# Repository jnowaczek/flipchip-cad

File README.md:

# flipchip-cad

## MM24I Extended Memory
NVSRAM-based replacement for 24 kiloword PDP-12 core memory expansion normally accomplished with an expansion chassis and up to 6 MM8I modules. This design is potentially compatible with PDP-8i machines, although the memory timing signals are slightly different. Requires appropriate Memory Extension Control module (MC12 for the PDP-12).

## Signal Cable Connector W021J
Flat-flex cable version of the W021 intended for use with the MM24I

## Flip Chip Slot Breakout P111
First attempt at PCB design, intended to simplify probing a PDP backplane with an oscilloscope

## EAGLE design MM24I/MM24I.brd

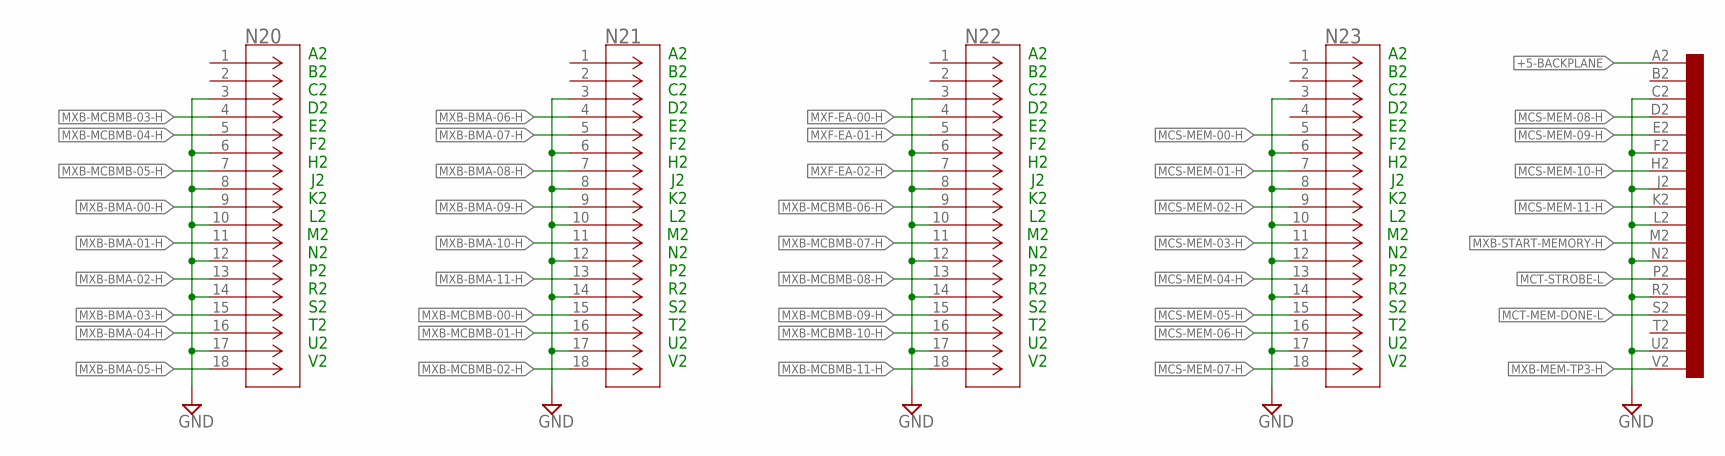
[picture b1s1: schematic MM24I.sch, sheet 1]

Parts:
N20, N21, N22, N23: FH12-18S-0.5SV(55); CON18_1X18_DUTB_HRS
U$1: SINGLE; EDGE-CON2

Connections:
+5-BACKPLANE: U$1.A2; also elsewhere on the board
GND: N20.3, N20.6, N20.8, N20.10, N20.12, N20.14, N20.17, N21.3, N21.6, N21.8, N21.10, N21.12, N21.14, N21.17, N22.3, N22.6, N22.8, N22.10, N22.12, N22.14, N22.17, N23.3, N23.6, N23.8, N23.10, N23.12, N23.14, N23.17, U$1.C2, U$1.F2, U$1.J2, U$1.L2, U$1.N2, U$1.R2, U$1.U2; also elsewhere on the board
MCS-MEM-00-H: N23.5; also elsewhere on the board
MCS-MEM-01-H: N23.7; also elsewhere on the board
MCS-MEM-02-H: N23.9; also elsewhere on the board
MCS-MEM-03-H: N23.11; also elsewhere on the board
MCS-MEM-04-H: N23.13; also elsewhere on the board
MCS-MEM-05-H: N23.15; also elsewhere on the board
MCS-MEM-06-H: N23.16; also elsewhere on the board
MCS-MEM-07-H: N23.18; also elsewhere on the board
MCS-MEM-08-H: U$1.D2; also elsewhere on the board
MCS-MEM-09-H: U$1.E2; also elsewhere on the board
MCS-MEM-10-H: U$1.H2; also elsewhere on the board
MCS-MEM-11-H: U$1.K2; also elsewhere on the board
MCT-MEM-DONE-L: U$1.S2; also elsewhere on the board
MCT-STROBE-L: U$1.P2; also elsewhere on the board
MXB-BMA-00-H: N20.9; also elsewhere on the board
MXB-BMA-01-H: N20.11; also elsewhere on the board
MXB-BMA-02-H: N20.13; also elsewhere on the board
MXB-BMA-03-H: N20.15; also elsewhere on the board
MXB-BMA-04-H: N20.16; also elsewhere on the board
MXB-BMA-05-H: N20.18; also elsewhere on the board
MXB-BMA-06-H: N21.4; also elsewhere on the board
MXB-BMA-07-H: N21.5; also elsewhere on the board
MXB-BMA-08-H: N21.7; also elsewhere on the board
MXB-BMA-09-H: N21.9; also elsewhere on the board
MXB-BMA-10-H: N21.11; also elsewhere on the board
MXB-BMA-11-H: N21.13; also elsewhere on the board
MXB-MCBMB-00-H: N21.15; also elsewhere on the board
MXB-MCBMB-01-H: N21.16; also elsewhere on the board
MXB-MCBMB-02-H: N21.18; also elsewhere on the board
MXB-MCBMB-03-H: N20.4; also elsewhere on the board
MXB-MCBMB-04-H: N20.5; also elsewhere on the board
MXB-MCBMB-05-H: N20.7; also elsewhere on the board
MXB-MCBMB-06-H: N22.9; also elsewhere on the board
MXB-MCBMB-07-H: N22.11; also elsewhere on the board
MXB-MCBMB-08-H: N22.13; also elsewhere on the board
MXB-MCBMB-09-H: N22.15; also elsewhere on the board
MXB-MCBMB-10-H: N22.16; also elsewhere on the board
MXB-MCBMB-11-H: N22.18; also elsewhere on the board
MXB-MEM-TP3-H: U$1.V2; also elsewhere on the board
MXB-START-MEMORY-H: U$1.M2; also elsewhere on the board
MXF-EA-00-H: N22.4; also elsewhere on the board
MXF-EA-01-H: N22.5; also elsewhere on the board
MXF-EA-02-H: N22.7; also elsewhere on the board

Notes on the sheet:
A2 B2 C2 D2 E2 F2 H2 J2 K2 L2 M2 N2 P2 R2 S2 T2 U2 V2

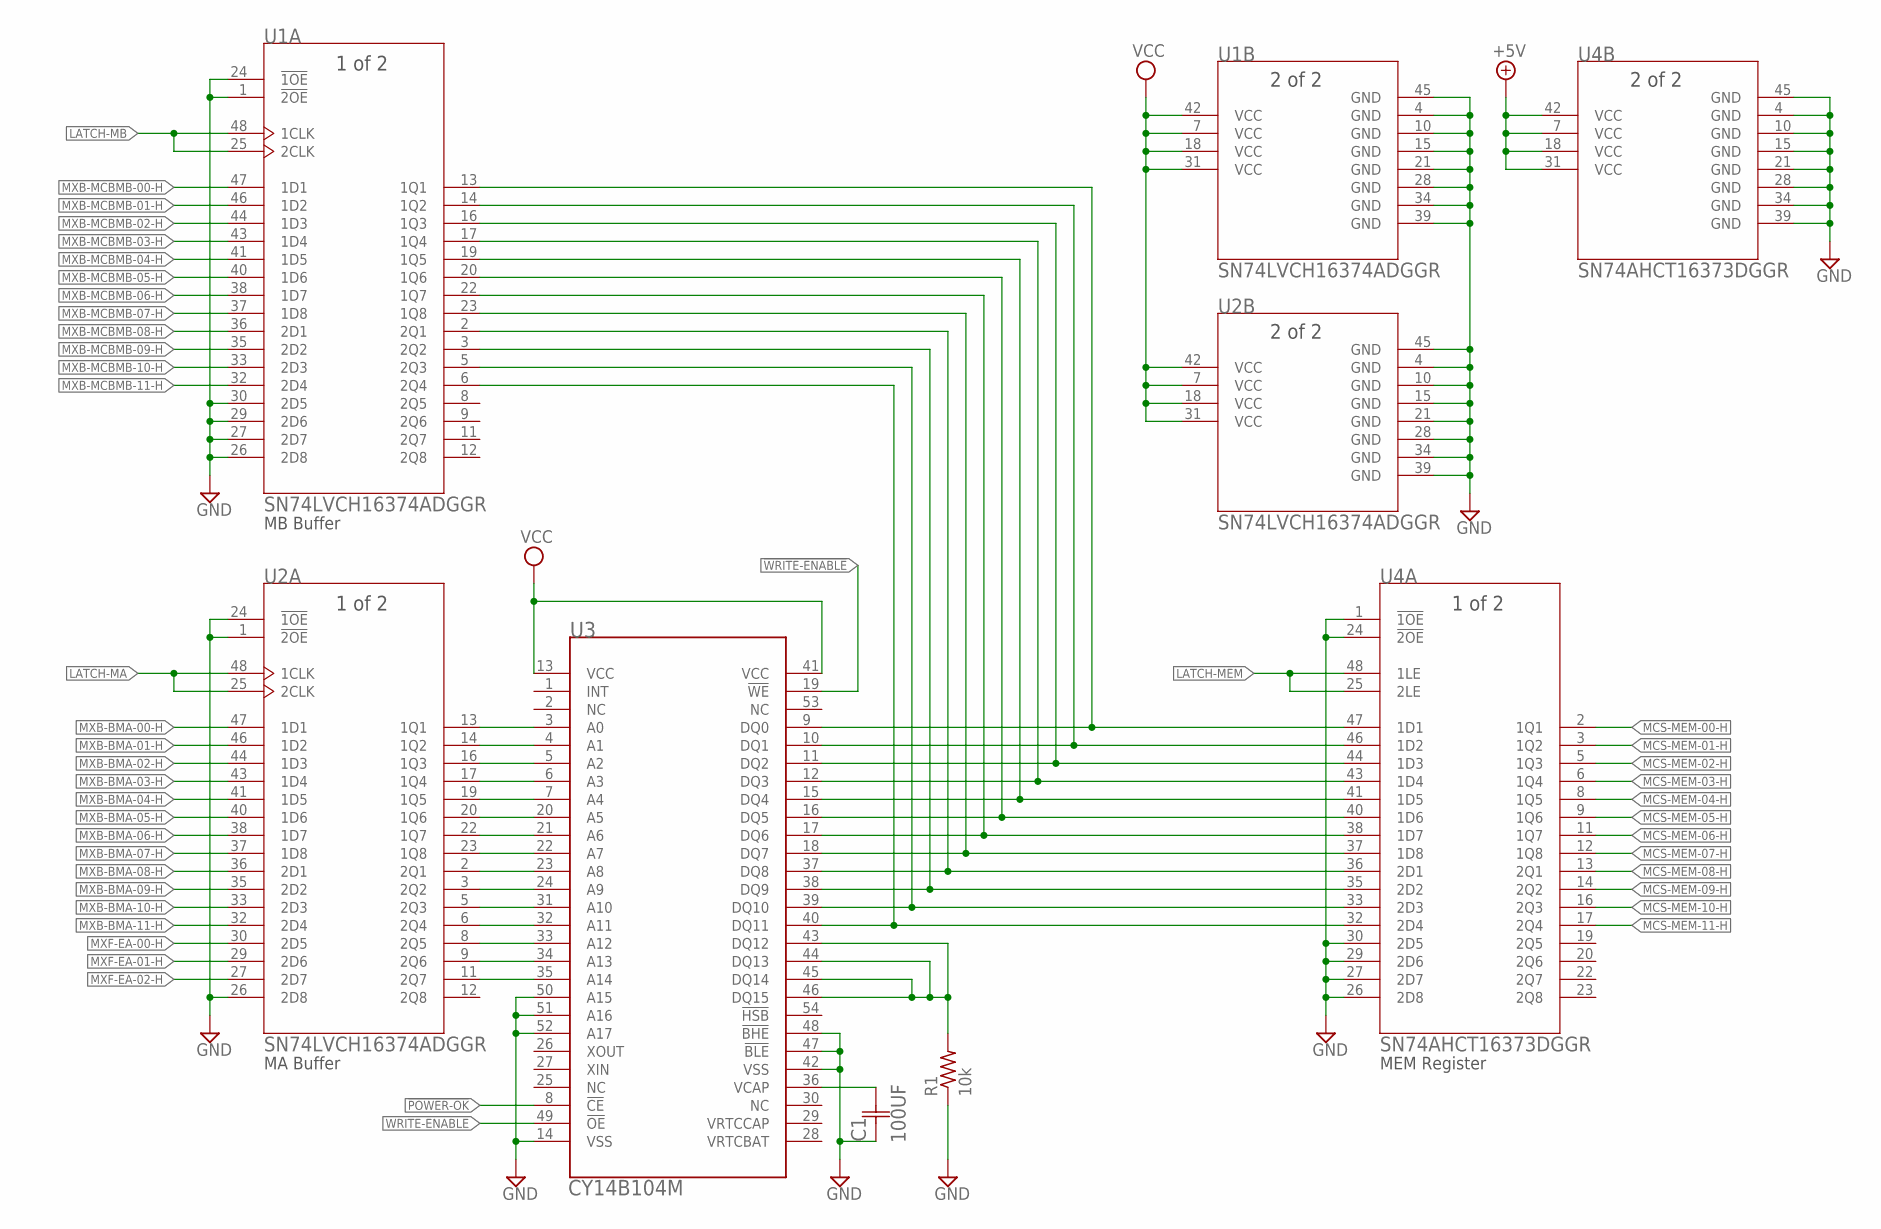
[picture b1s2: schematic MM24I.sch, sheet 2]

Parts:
C1: 100UF; CAPCP7343X430N
R1: 10k; R0402
U1, U2: SN74LVCH16374ADGGR; DGG48
U3: CY14B104M; TSOPII-54
U4: SN74AHCT16373DGGR; DGG48

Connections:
!POWER-OK: U3.8 (!CE); also elsewhere on the board
!WRITE-ENABLE: U3.19 (!WE); also elsewhere on the board
+5V: U4.7 (VCC), U4.18 (VCC), U4.31 (VCC), U4.42 (VCC); also elsewhere on the board
GND: C1.2 (C2), R1.1, U1.1 (!2OE), U1.4 (GND), U1.10 (GND), U1.15 (GND), U1.21 (GND), U1.24 (!1OE), U1.26 (2D8), U1.27 (2D7), U1.28 (GND), U1.29 (2D6), U1.30 (2D5), U1.34 (GND), U1.39 (GND), U1.45 (GND), U2.1 (!2OE), U2.4 (GND), U2.10 (GND), U2.15 (GND), U2.21 (GND), U2.24 (!1OE), U2.26 (2D8), U2.28 (GND), U2.34 (GND), U2.39 (GND), U2.45 (GND), U3.14 (VSS), U3.42 (VSS), U3.47 (!BLE), U3.48 (!BHE), U3.50 (A15), U3.51 (A16), U3.52 (A17), U4.1 (!1OE), U4.4 (GND), U4.10 (GND), U4.15 (GND), U4.21 (GND), U4.24 (!2OE), U4.26 (2D8), U4.27 (2D7), U4.28 (GND), U4.29 (2D6), U4.30 (2D5), U4.34 (GND), U4.39 (GND), U4.45 (GND); also elsewhere on the board
LATCH-MA: U2.25 (2CLK), U2.48 (1CLK); also elsewhere on the board
LATCH-MB: U1.25 (2CLK), U1.48 (1CLK); also elsewhere on the board
LATCH-MEM: U4.25 (2LE), U4.48 (1LE); also elsewhere on the board
MCS-MEM-00-H: U4.2 (1Q1); also elsewhere on the board
MCS-MEM-01-H: U4.3 (1Q2); also elsewhere on the board
MCS-MEM-02-H: U4.5 (1Q3); also elsewhere on the board
MCS-MEM-03-H: U4.6 (1Q4); also elsewhere on the board
MCS-MEM-04-H: U4.8 (1Q5); also elsewhere on the board
MCS-MEM-05-H: U4.9 (1Q6); also elsewhere on the board
MCS-MEM-06-H: U4.11 (1Q7); also elsewhere on the board
MCS-MEM-07-H: U4.12 (1Q8); also elsewhere on the board
MCS-MEM-08-H: U4.13 (2Q1); also elsewhere on the board
MCS-MEM-09-H: U4.14 (2Q2); also elsewhere on the board
MCS-MEM-10-H: U4.16 (2Q3); also elsewhere on the board
MCS-MEM-11-H: U4.17 (2Q4); also elsewhere on the board
MXB-BMA-00-H: U2.47 (1D1); also elsewhere on the board
MXB-BMA-01-H: U2.46 (1D2); also elsewhere on the board
MXB-BMA-02-H: U2.44 (1D3); also elsewhere on the board
MXB-BMA-03-H: U2.43 (1D4); also elsewhere on the board
MXB-BMA-04-H: U2.41 (1D5); also elsewhere on the board
MXB-BMA-05-H: U2.40 (1D6); also elsewhere on the board
MXB-BMA-06-H: U2.38 (1D7); also elsewhere on the board
MXB-BMA-07-H: U2.37 (1D8); also elsewhere on the board
MXB-BMA-08-H: U2.36 (2D1); also elsewhere on the board
MXB-BMA-09-H: U2.35 (2D2); also elsewhere on the board
MXB-BMA-10-H: U2.33 (2D3); also elsewhere on the board
MXB-BMA-11-H: U2.32 (2D4); also elsewhere on the board
MXB-MCBMB-00-H: U1.47 (1D1); also elsewhere on the board
MXB-MCBMB-01-H: U1.46 (1D2); also elsewhere on the board
MXB-MCBMB-02-H: U1.44 (1D3); also elsewhere on the board
MXB-MCBMB-03-H: U1.43 (1D4); also elsewhere on the board
MXB-MCBMB-04-H: U1.41 (1D5); also elsewhere on the board
MXB-MCBMB-05-H: U1.40 (1D6); also elsewhere on the board
MXB-MCBMB-06-H: U1.38 (1D7); also elsewhere on the board
MXB-MCBMB-07-H: U1.37 (1D8); also elsewhere on the board
MXB-MCBMB-08-H: U1.36 (2D1); also elsewhere on the board
MXB-MCBMB-09-H: U1.35 (2D2); also elsewhere on the board
MXB-MCBMB-10-H: U1.33 (2D3); also elsewhere on the board
MXB-MCBMB-11-H: U1.32 (2D4); also elsewhere on the board
MXF-EA-00-H: U2.30 (2D5); also elsewhere on the board
MXF-EA-01-H: U2.29 (2D6); also elsewhere on the board
MXF-EA-02-H: U2.27 (2D7); also elsewhere on the board
unnamed: U1.13 (1Q1), U3.9 (DQ0), U4.47 (1D1)
unnamed: U1.14 (1Q2), U3.10 (DQ1), U4.46 (1D2)
unnamed: U1.16 (1Q3), U3.11 (DQ2), U4.44 (1D3)
unnamed: U1.17 (1Q4), U3.12 (DQ3), U4.43 (1D4)
unnamed: U1.19 (1Q5), U3.15 (DQ4), U4.41 (1D5)
unnamed: U1.20 (1Q6), U3.16 (DQ5), U4.40 (1D6)
unnamed: R1.2, U3.43 (DQ12), U3.44 (DQ13), U3.45 (DQ14), U3.46 (DQ15)
unnamed: U1.22 (1Q7), U3.17 (DQ6), U4.38 (1D7)
unnamed: U1.23 (1Q8), U3.18 (DQ7), U4.37 (1D8)
unnamed: U1.2 (2Q1), U3.37 (DQ8), U4.36 (2D1)
unnamed: U1.3 (2Q2), U3.38 (DQ9), U4.35 (2D2)
unnamed: U1.5 (2Q3), U3.39 (DQ10), U4.33 (2D3)
unnamed: U1.6 (2Q4), U3.40 (DQ11), U4.32 (2D4)
unnamed: U2.2 (2Q1), U3.23 (A8)
unnamed: U2.16 (1Q3), U3.5 (A2)
unnamed: U2.13 (1Q1), U3.3 (A0)
unnamed: U2.14 (1Q2), U3.4 (A1)
unnamed: U2.17 (1Q4), U3.6 (A3)
unnamed: U2.19 (1Q5), U3.7 (A4)
unnamed: U2.20 (1Q6), U3.20 (A5)
unnamed: U2.22 (1Q7), U3.21 (A6)
unnamed: U2.23 (1Q8), U3.22 (A7)
unnamed: U2.3 (2Q2), U3.24 (A9)
unnamed: U2.5 (2Q3), U3.31 (A10)
unnamed: U2.6 (2Q4), U3.32 (A11)
unnamed: U2.8 (2Q5), U3.33 (A12)
unnamed: U2.9 (2Q6), U3.34 (A13)
unnamed: U2.11 (2Q7), U3.35 (A14)
VCAP: C1.1 (C1), U3.36 (VCAP)
VCC: U1.7 (VCC), U1.18 (VCC), U1.31 (VCC), U1.42 (VCC), U2.7 (VCC), U2.18 (VCC), U2.31 (VCC), U2.42 (VCC), U3.13 (VCC), U3.41 (VCC); also elsewhere on the board
WRITE-ENABLE: U3.49 (!OE); also elsewhere on the board

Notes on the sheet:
MEM Register
MB Buffer
MA Buffer

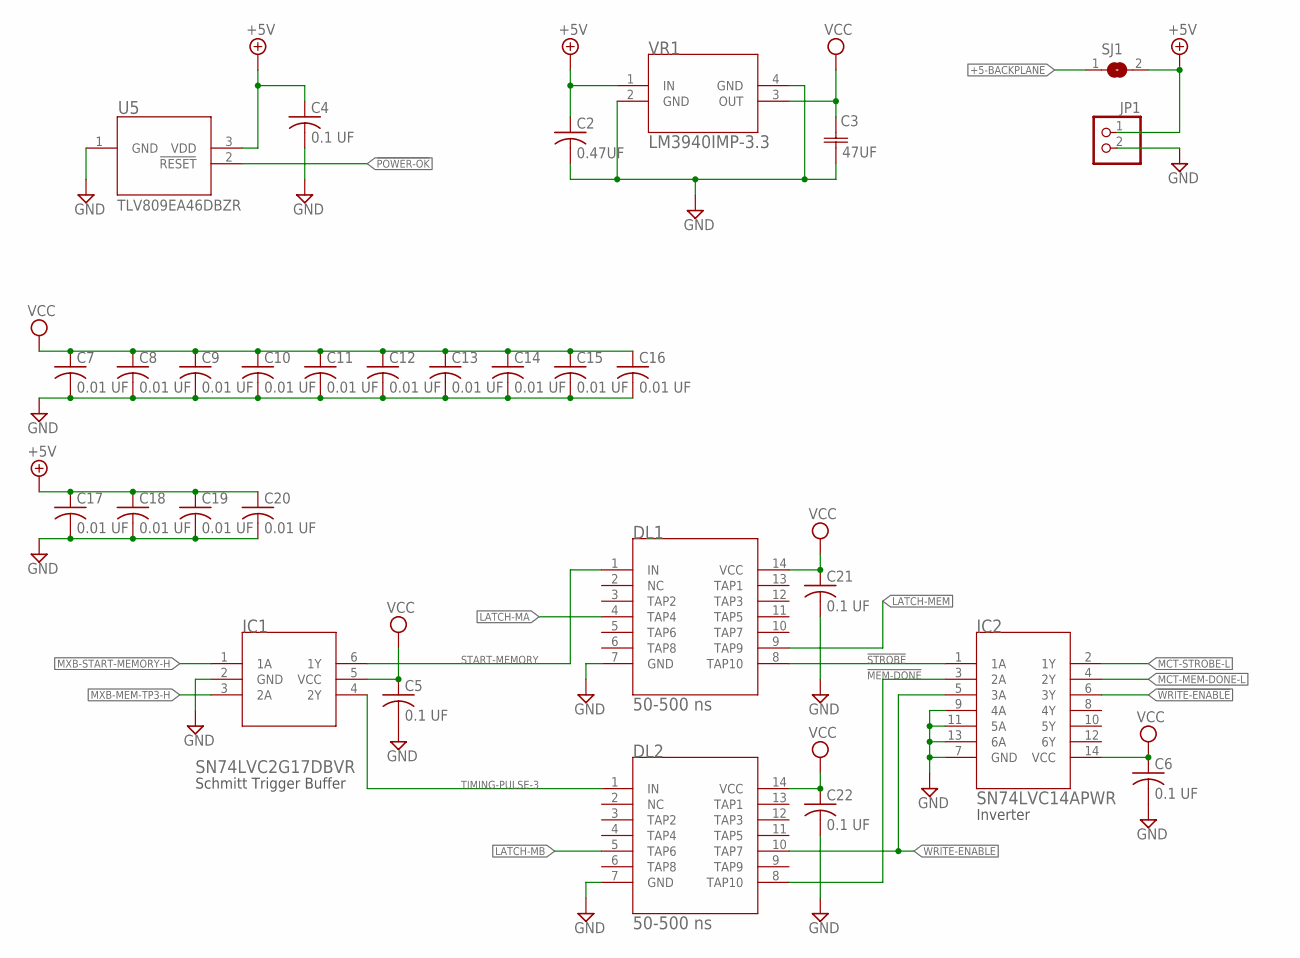
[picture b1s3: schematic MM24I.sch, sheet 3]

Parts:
C2: 0.47UF; C0805
C3: 47UF; NOJC
C4, C5, C6, C21, C22: 0.1 UF; C0402
C7, C8, C9, C10, C11, C12, C13, C14, C15, C16, C17, C18, C19, C20: 0.01 UF; C0402
DL1, DL2: 50-500 ns; 21-0066J_14
IC1: SN74LVC2G17DBVR; DBV6
IC2: SN74LVC14APWR; PW14
JP1: PINHD-1X2; 1X02
SJ1: SJ
U5: TLV809EA46DBZR; DBZ3
VR1: LM3940IMP-3.3; MP04A

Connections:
!MEM-DONE: DL2.8 (TAP10), IC2.3 (2A)
!POWER-OK: U5.2 (!RESET); also elsewhere on the board
!STROBE: DL1.8 (TAP10), IC2.1 (1A)
!WRITE-ENABLE: IC2.6 (3Y); also elsewhere on the board
+5-BACKPLANE: SJ1.1; also elsewhere on the board
+5V: C2.1, C4.1, C17.1, C18.1, C19.1, C20.1, JP1.1, SJ1.2, U5.3 (VDD), VR1.1 (IN); also elsewhere on the board
GND: C2.2, C3.2 (C2), C4.2, C5.2, C6.2, C7.2, C8.2, C9.2, C10.2, C11.2, C12.2, C13.2, C14.2, C15.2, C16.2, C17.2, C18.2, C19.2, C20.2, C21.2, C22.2, DL1.7 (GND), DL2.7 (GND), IC1.2 (GND), IC2.7 (GND), IC2.9 (4A), IC2.11 (5A), IC2.13 (6A), JP1.2, U5.1 (GND), VR1.2 (GND), VR1.4 (GND); also elsewhere on the board
LATCH-MA: DL1.4 (TAP4); also elsewhere on the board
LATCH-MB: DL2.5 (TAP6); also elsewhere on the board
LATCH-MEM: DL1.9 (TAP9); also elsewhere on the board
MCT-MEM-DONE-L: IC2.4 (2Y); also elsewhere on the board
MCT-STROBE-L: IC2.2 (1Y); also elsewhere on the board
MXB-MEM-TP3-H: IC1.3 (2A); also elsewhere on the board
MXB-START-MEMORY-H: IC1.1 (1A); also elsewhere on the board
START-MEMORY: DL1.1 (IN), IC1.6 (1Y)
TIMING-PULSE-3: DL2.1 (IN), IC1.4 (2Y)
VCC: C3.1 (C1), C5.1, C6.1, C7.1, C8.1, C9.1, C10.1, C11.1, C12.1, C13.1, C14.1, C15.1, C16.1, C21.1, C22.1, DL1.14 (VCC), DL2.14 (VCC), IC1.5 (VCC), IC2.14 (VCC), VR1.3 (OUT); also elsewhere on the board
WRITE-ENABLE: DL2.10 (TAP7), IC2.5 (3A); also elsewhere on the board

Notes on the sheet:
Schmitt Trigger Buffer
Inverter

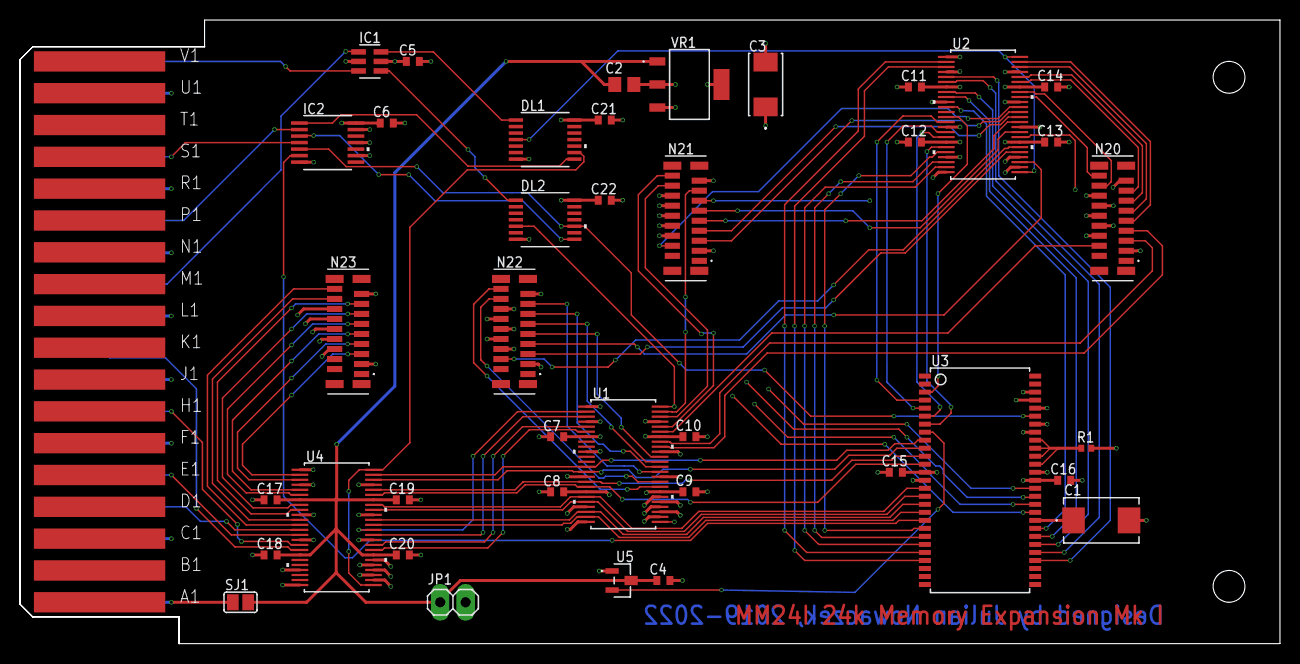
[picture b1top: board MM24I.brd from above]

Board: 4 copper layers, 125.7 x 62.2 mm, 41 parts (0 on the bottom side), 86 nets.

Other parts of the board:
U$2: SINGLE

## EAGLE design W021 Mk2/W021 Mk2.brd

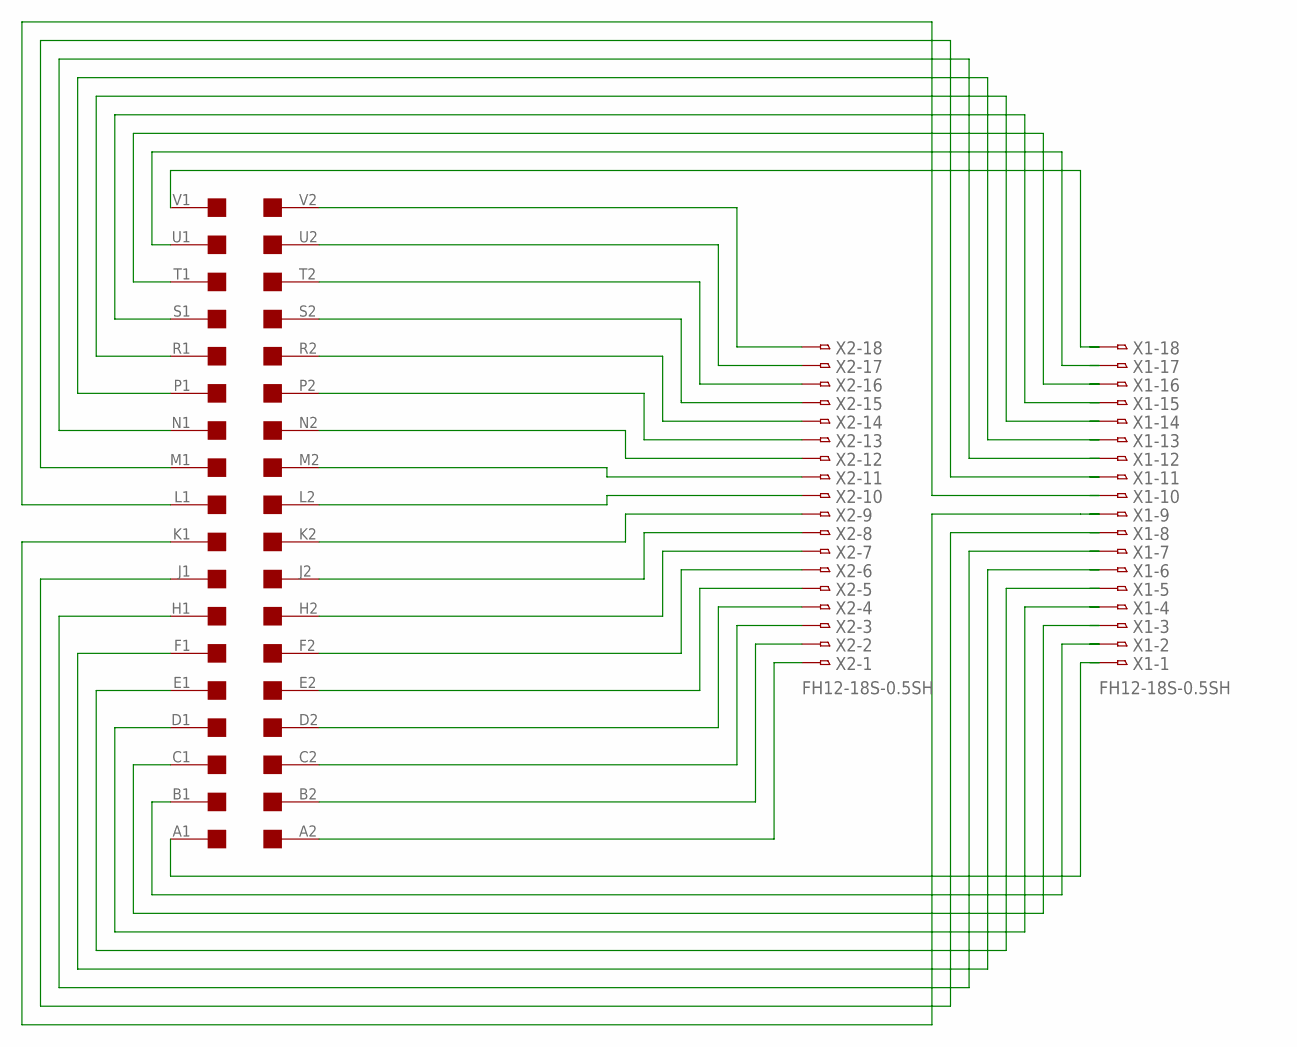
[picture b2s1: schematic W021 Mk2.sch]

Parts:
EDGE1: EDGE-2CONNECTOR; EDGE-CON2
X1, X2: FH12-18S-0.5SH

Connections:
unnamed: EDGE1.V2, X2.18
unnamed: EDGE1.U2, X2.17
unnamed: EDGE1.T2, X2.16
unnamed: EDGE1.S2, X2.15
unnamed: EDGE1.R2, X2.14
unnamed: EDGE1.P2, X2.13
unnamed: EDGE1.N2, X2.12
unnamed: EDGE1.M2, X2.11
unnamed: EDGE1.L2, X2.10
unnamed: EDGE1.K2, X2.9
unnamed: EDGE1.J2, X2.8
unnamed: EDGE1.H2, X2.7
unnamed: EDGE1.F2, X2.6
unnamed: EDGE1.E2, X2.5
unnamed: EDGE1.D2, X2.4
unnamed: EDGE1.C2, X2.3
unnamed: EDGE1.B2, X2.2
unnamed: EDGE1.V1, X1.18
unnamed: EDGE1.U1, X1.17
unnamed: EDGE1.T1, X1.16
unnamed: EDGE1.R1, X1.14
unnamed: EDGE1.N1, X1.12
unnamed: EDGE1.L1, X1.10
unnamed: EDGE1.D1, X1.4
unnamed: EDGE1.E1, X1.5
unnamed: EDGE1.F1, X1.6
unnamed: EDGE1.A2, X2.1
unnamed: EDGE1.M1, X1.11
unnamed: EDGE1.S1, X1.15
unnamed: EDGE1.P1, X1.13
unnamed: EDGE1.K1, X1.9
unnamed: EDGE1.J1, X1.8
unnamed: EDGE1.H1, X1.7
unnamed: EDGE1.C1, X1.3

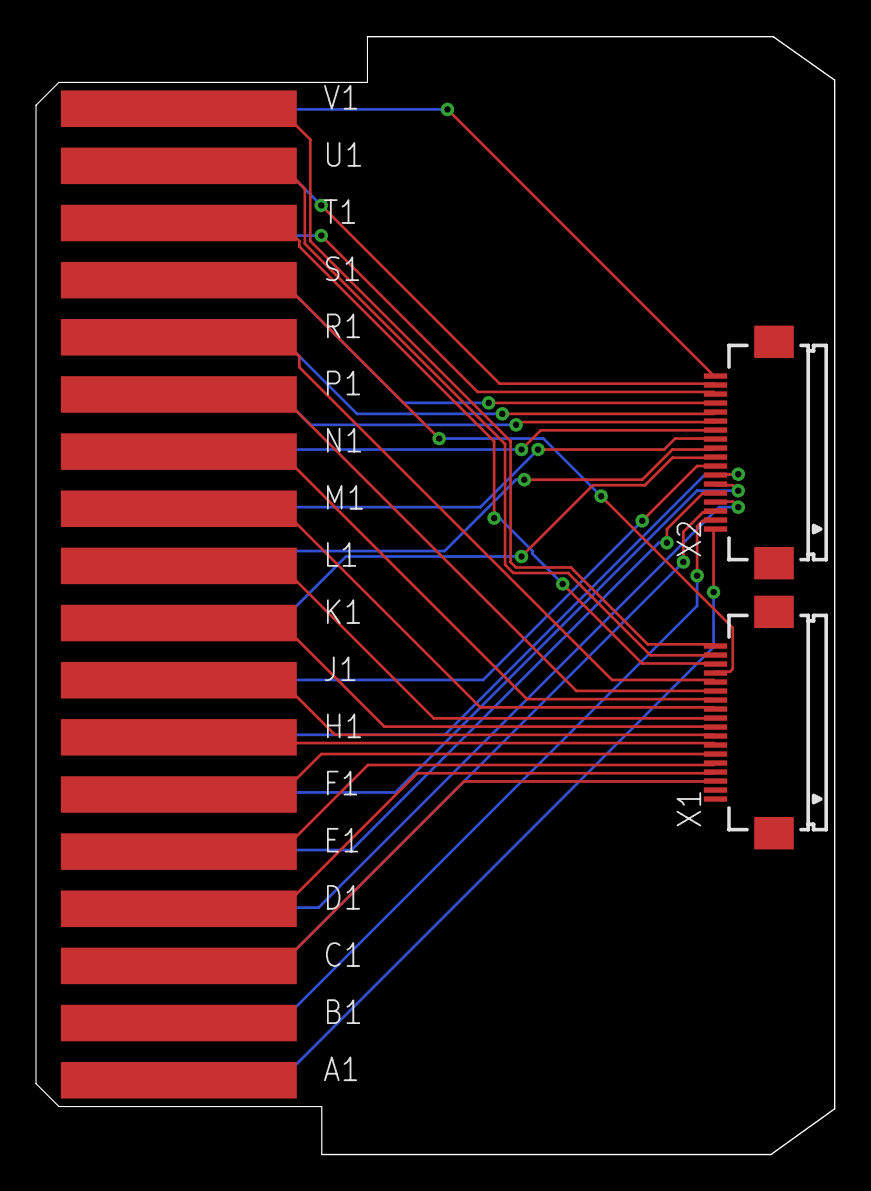
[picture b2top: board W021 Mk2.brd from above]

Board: 2 copper layers, 44.4 x 62.1 mm, 3 parts (0 on the bottom side), 34 nets.

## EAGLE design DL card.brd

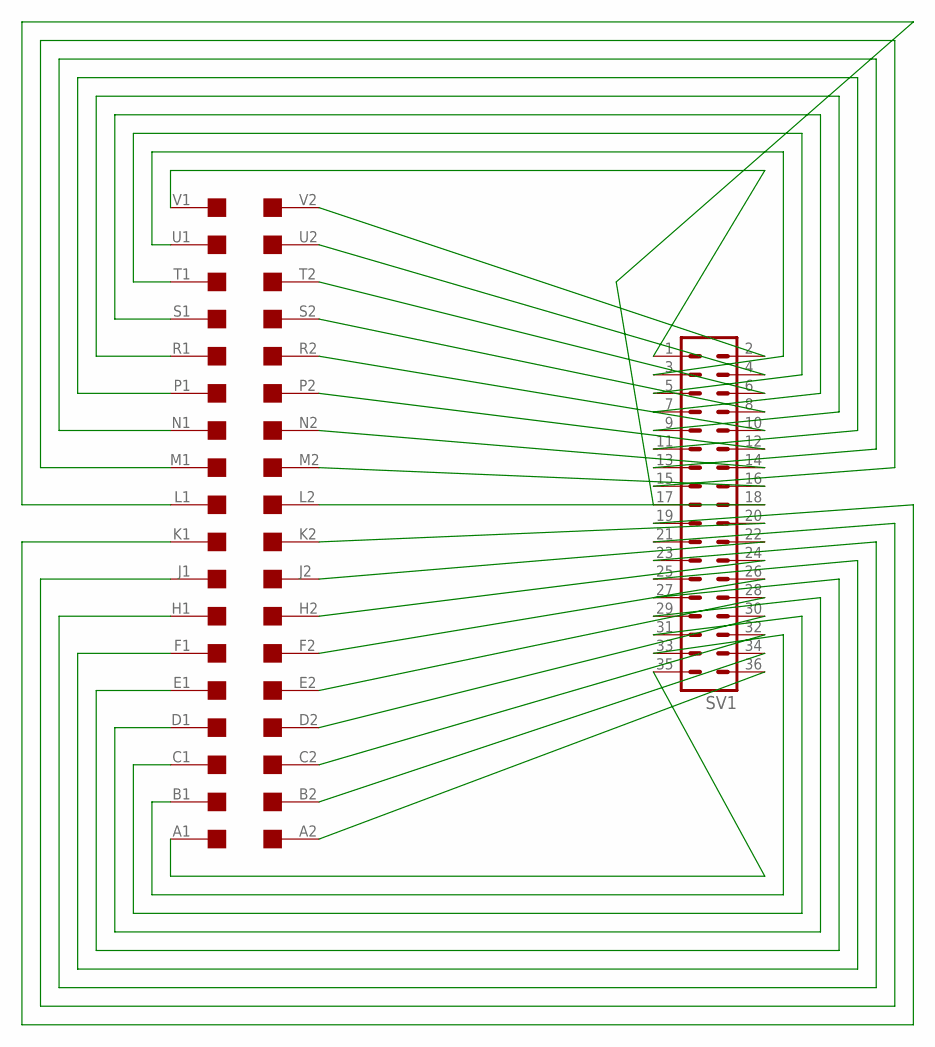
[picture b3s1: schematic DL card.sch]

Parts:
EDGE1: EDGE-2CONNECTOR; EDGE-CON2
SV1: MA18-2W

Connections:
unnamed: EDGE1.V2, SV1.2
unnamed: EDGE1.U2, SV1.4
unnamed: EDGE1.T2, SV1.6
unnamed: EDGE1.S2, SV1.8
unnamed: EDGE1.R2, SV1.10
unnamed: EDGE1.P2, SV1.12
unnamed: EDGE1.N2, SV1.14
unnamed: EDGE1.M2, SV1.16
unnamed: EDGE1.L2, SV1.18
unnamed: EDGE1.K2, SV1.20
unnamed: EDGE1.J2, SV1.22
unnamed: EDGE1.H2, SV1.24
unnamed: EDGE1.F2, SV1.26
unnamed: EDGE1.E2, SV1.28
unnamed: EDGE1.D2, SV1.30
unnamed: EDGE1.C2, SV1.32
unnamed: EDGE1.B2, SV1.34
unnamed: EDGE1.A2, SV1.36
unnamed: EDGE1.V1, SV1.1
unnamed: EDGE1.U1, SV1.3
unnamed: EDGE1.T1, SV1.5
unnamed: EDGE1.S1, SV1.7
unnamed: EDGE1.R1, SV1.9
unnamed: EDGE1.N1, SV1.13
unnamed: EDGE1.P1, SV1.11
unnamed: EDGE1.A1, SV1.35
unnamed: EDGE1.B1, SV1.33
unnamed: EDGE1.C1, SV1.31
unnamed: EDGE1.D1, SV1.29
unnamed: EDGE1.E1, SV1.27
unnamed: EDGE1.F1, SV1.25
unnamed: EDGE1.H1, SV1.23
unnamed: EDGE1.M1, SV1.15
unnamed: EDGE1.J1, SV1.21
unnamed: EDGE1.L1, SV1.17
unnamed: EDGE1.K1, SV1.19

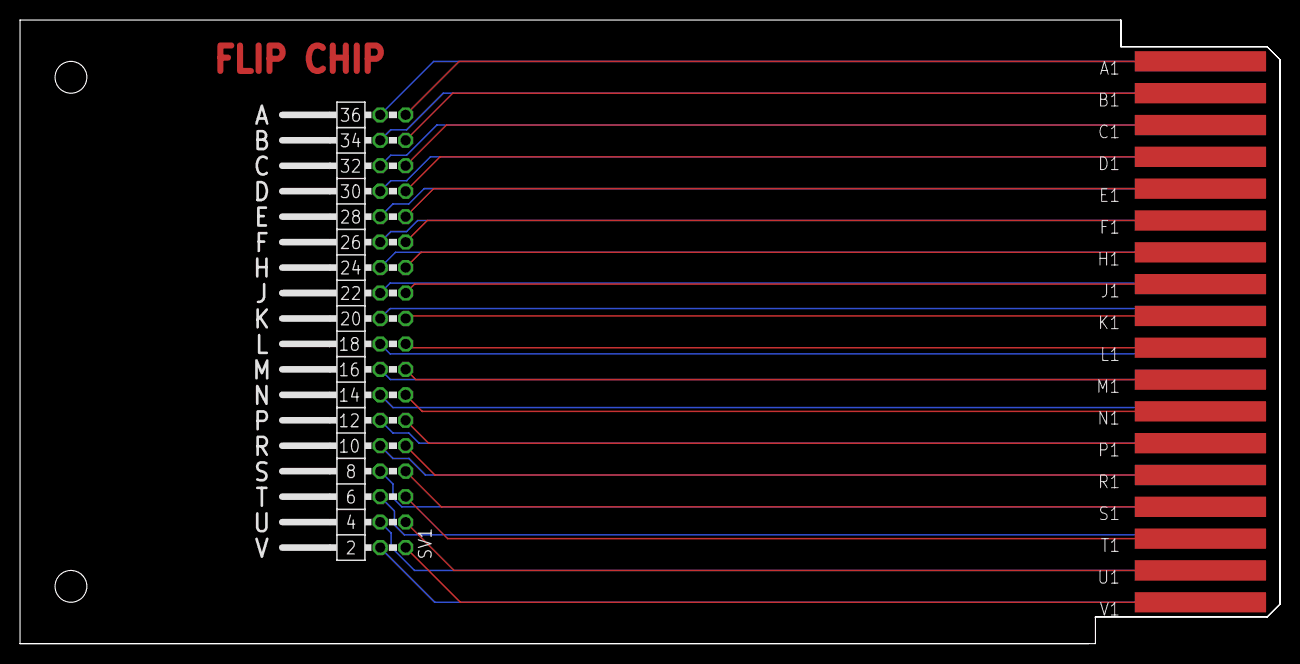
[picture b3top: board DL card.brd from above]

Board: 2 copper layers, 125.7 x 62.2 mm, 4 parts (0 on the bottom side), 36 nets.

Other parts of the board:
U$1: SINGLE-R
U$2: FLIPCHIP

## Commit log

2019-06-09 Shrank P111 area to reduce cost
2019-11-09 Beginning memory expansion work
2019-11-10 Add SN74LVC16T245 16-bit Bus Transceiver/Level Shifter
2019-11-26 Progress on MM8I Mk2
2019-11-30 First board layout revision
2020-01-02 Redesigned memory expansion to fit on a single flip chip, consolidated component libraries, etc.
2020-01-02 Fix typo in , change FFC reference designators to match backplane slot names on MM24I
2022-01-08 Add bypass capacitors to schematic
2022-02-15 Added bypass capacitors, reworked W021J
2022-02-21 Rework MM24I voltage supervisor
2022-02-22 Disable thermals on pours to work around EAGLE bug
2022-02-22 Update W021J renders
2022-03-04 Bump EAGLE project file version
2022-03-04 Ignore backup files
